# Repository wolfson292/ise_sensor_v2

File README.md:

# ise_sensor_v2
Open Source Isolated I2C ISE Sensor

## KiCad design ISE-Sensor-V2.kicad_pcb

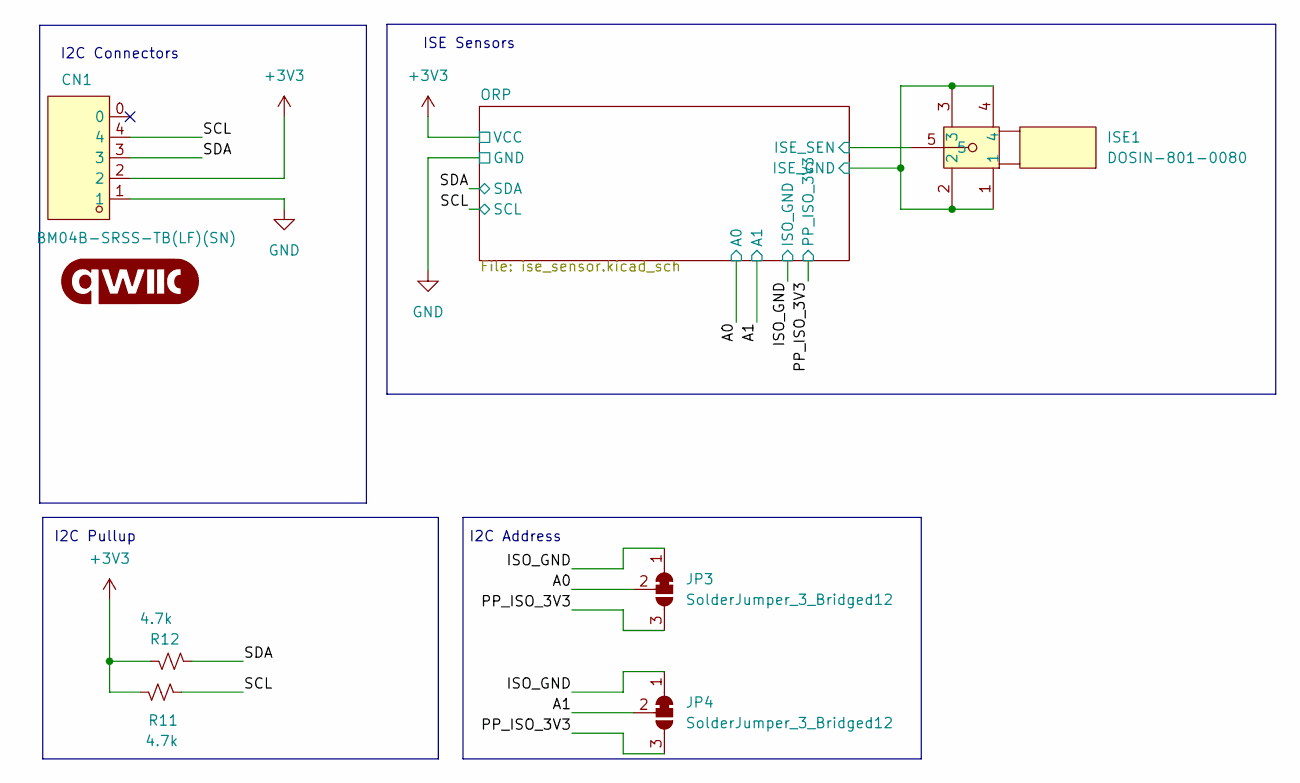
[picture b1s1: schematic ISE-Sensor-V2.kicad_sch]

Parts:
CN1: BM04B-SRSS-TB(LF)(SN); CONN-SMD_BM04B-SRSS-TB; LCSC Part C160390
G1: qwiic_Logo
ISE1: DOSIN-801-0080; BNC-TH_DOSIN-801-0080; LCSC Part C521219
JP3, JP4: SolderJumper_3_Bridged12; SolderJumper-3_P1.3mm_Bridged12_RoundedPad1.0x1.5mm
R11, R12: 4.7k; R_0402_1005Metric; MPN 4.7k 0201

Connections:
+3V3: CN1.2, R11.1, R12.2; also elsewhere on the board
/A0: JP3.2 (C); also elsewhere on the board
/A1: JP4.2 (C); also elsewhere on the board
/ISO_GND: ISE1.1, ISE1.2, ISE1.3, ISE1.4, JP3.1 (A), JP4.1 (A); also elsewhere on the board
/ORP/ISE_SEN: ISE1.5; also elsewhere on the board
/PP_ISO_3V3: JP3.3 (B), JP4.3 (B); also elsewhere on the board
/SCL: CN1.4, R11.2; also elsewhere on the board
/SDA: CN1.3, R12.1; also elsewhere on the board
GND: CN1.1; also elsewhere on the board

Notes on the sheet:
ISE Sensors
I2C Pullup
I2C Connectors
I2C Address

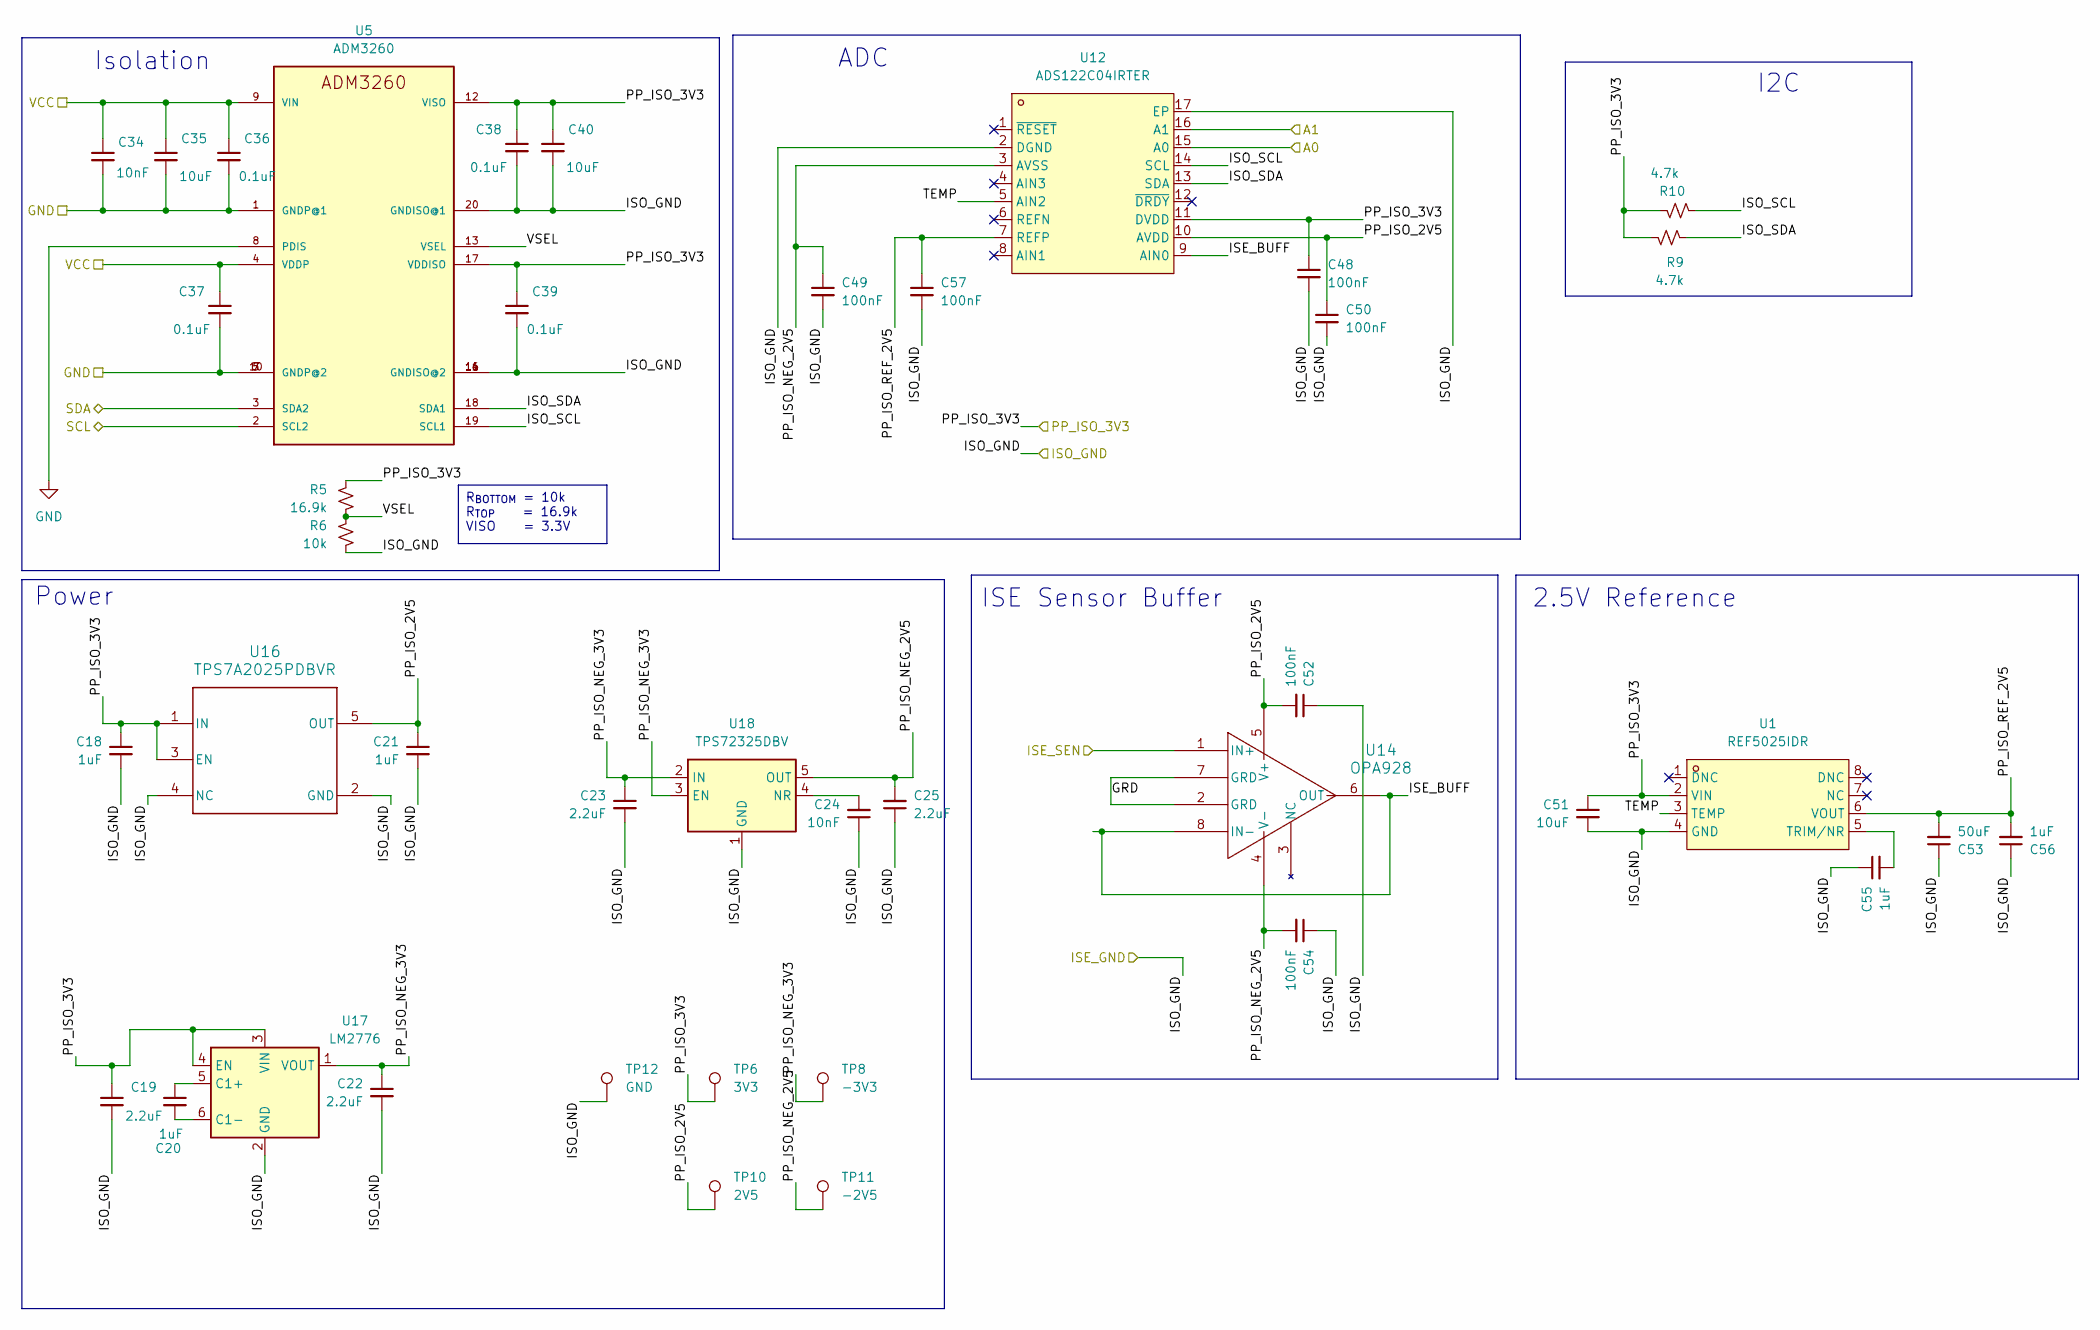
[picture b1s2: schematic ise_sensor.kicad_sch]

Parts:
C18, C20, C21: 1uF; C_0402_1005Metric; MPN 1uF 0201
C19, C22: 2.2uF; C_0402_1005Metric; MPN 1uF 0201
C23, C25: 2.2uF; C_0402_1005Metric; MPN 2.2uF 0201
C24, C34: 10nF; C_0402_1005Metric; MPN 10nF 0201
C35, C40: 10uF; C_0402_1005Metric; MPN 10uF 0201
C36, C37, C38, C39: 0.1uF; C_0402_1005Metric; MPN 0.1uF 0201
C48, C49, C50, C57: 100nF; C_0402_1005Metric; MPN 100nF 0201
C51: 10uF; C_0402_1005Metric; MPN 100nF 0201
C52, C54: 100nF; C_0402_1005Metric
C53: 50uF; C_0402_1005Metric; MPN 100nF 0201
C55, C56: 1uF; C_0402_1005Metric; MPN 100nF 0201
R5: 16.9k; R_0402_1005Metric; MPN 30.9k 0201
R6: 10k; R_0402_1005Metric; MPN 10k 0201
R9, R10: 4.7k; R_0402_1005Metric; MPN 4.7k 0201
TP6: 3V3; TestPoint_Pad_D1.0mm
TP8: -3V3; TestPoint_Pad_D1.0mm
TP10: 2V5; TestPoint_Pad_D1.0mm
TP11: -2V5; TestPoint_Pad_D1.0mm
TP12: GND; TestPoint_Pad_D1.0mm
U1: REF5025IDR; SOIC-8_L4.9-W3.9-P1.27-LS6.0-BL; LCSC Part C544535
U5: ADM3260; ADM3260_SOP65P780X200-20N
U12: ADS122C04IRTER; WQFN-16_L3.0-W3.0-P0.50-TL-EP0.8; LCSC Part C2670105
U14: OPA928; SOIC8_D_TEX
U16: TPS7A2025PDBVR; DBV0005A-IPC_A
U17: LM2776; SOT-23-6
U18: TPS72325DBV; SOT-23-5

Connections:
+3V3: C34.1, C35.1, C36.1, C37.1, U5.4 (VDDP), U5.9 (VIN); also elsewhere on the board
/A0: U12.15 (A0); also elsewhere on the board
/A1: U12.16 (A1); also elsewhere on the board
/ISO_GND: C18.2, C19.2, C21.2, C22.2, C23.2, C24.1, C25.1, C38.2, C39.2, C40.2, C48.2, C49.2, C50.2, C51.2, C52.1, C53.1, C54.1, C55.1, C56.1, C57.2, R6.2, TP12.1, U1.4 (GND), U5.11 (GNDISO@2), U5.14 (GNDISO@2), U5.16 (GNDISO@2), U5.20 (GNDISO@1), U12.2 (DGND), U12.17 (EP), U16.2 (GND), U16.4 (NC), U17.2 (GND), U18.1 (GND); also elsewhere on the board
/ORP/GRD: U14.2 (GRD), U14.7 (GRD)
/ORP/ISE_BUFF: U12.9 (AIN0), U14.6 (OUT), U14.8 (IN-)
/ORP/ISE_SEN: U14.1 (IN+); also elsewhere on the board
/ORP/ISO_SCL: R10.1, U5.19 (SCL1), U12.14 (SCL)
/ORP/ISO_SDA: R9.2, U5.18 (SDA1), U12.13 (SDA)
/ORP/PP_ISO_2V5: C21.1, C50.1, C52.2, TP10.1, U12.10 (AVDD), U14.5 (V+), U16.5 (OUT)
/ORP/PP_ISO_NEG_2V5: C25.2, C49.1, C54.2, TP11.1, U12.3 (AVSS), U14.4 (V-), U18.5 (OUT)
/ORP/PP_ISO_NEG_3V3: C22.1, C23.1, TP8.1, U17.1 (VOUT), U18.2 (IN), U18.3 (EN)
/ORP/PP_ISO_REF_2V5: C53.2, C56.2, C57.1, U1.6 (VOUT), U12.7 (REFP)
/ORP/TEMP: U1.3 (TEMP), U12.5 (AIN2)
/ORP/VSEL: R5.1, R6.1, U5.13 (VSEL)
/PP_ISO_3V3: C18.1, C19.1, C38.1, C39.1, C40.1, C48.1, C51.1, R5.2, R9.1, R10.2, TP6.1, U1.2 (VIN), U5.12 (VISO), U5.17 (VDDISO), U12.11 (DVDD), U16.1 (IN), U16.3 (EN), U17.3 (VIN), U17.4 (EN); also elsewhere on the board
/SCL: U5.2 (SCL2); also elsewhere on the board
/SDA: U5.3 (SDA2); also elsewhere on the board
GND: C34.2, C35.2, C36.2, C37.2, U5.1 (GNDP@1), U5.5 (GNDP@2), U5.7 (GNDP@2), U5.8 (PDIS), U5.10 (GNDP@2); also elsewhere on the board
unnamed: C55.2, U1.5 (TRIM/NR)
unnamed: C20.1, U17.5 (C1+)
unnamed: C20.2, U17.6 (C1-)
unnamed: C24.2, U18.4 (NR)

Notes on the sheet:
ADC
Power
I2C
ISE Sensor Buffer
Isolation
2.5V Reference
R_{BOTTOM} = 10k R_{TOP} = 16.9k VISO = 3.3V

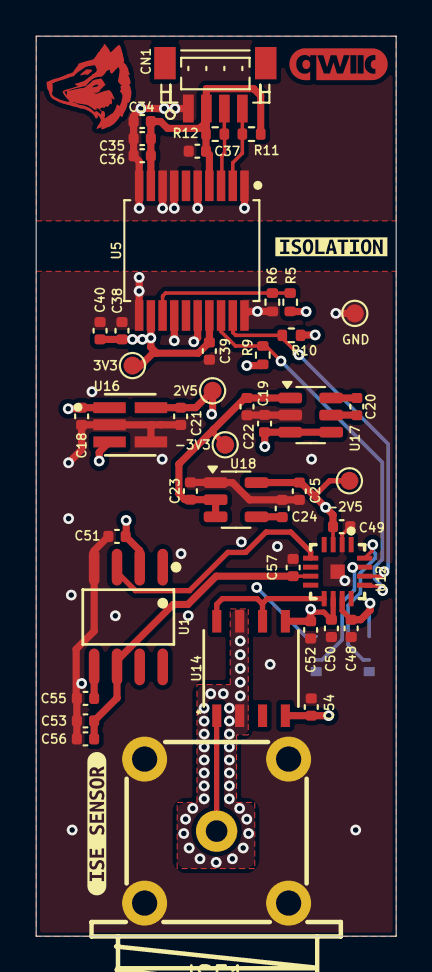
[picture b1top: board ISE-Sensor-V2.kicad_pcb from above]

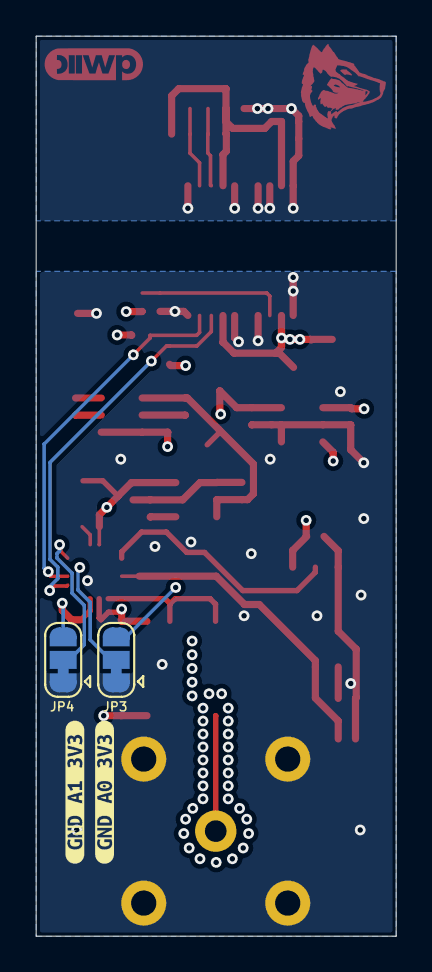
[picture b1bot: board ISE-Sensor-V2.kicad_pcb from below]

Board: 4 copper layers, 20.0 x 50.0 mm, 51 parts (4 on the bottom side), 23 nets.

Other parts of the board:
kibuzzard-67AA55A8: G***; kibuzzard-67AA55A8
kibuzzard-67AA55DF: G***; kibuzzard-67AA55DF
kibuzzard-67AA72AD: G***; kibuzzard-67AA72AD
kibuzzard-67B4F71A: G***; kibuzzard-67B4F71A

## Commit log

2025-02-13 Add output images
2025-02-13 Update images
